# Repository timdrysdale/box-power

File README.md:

# box-power
circuit schematic for iso-container in-box DC-DC convertor support board.

### i6A4W

The DC-DC convertor is an adjustable, 250W, 9 to 53V Input Non-Isolated Step Down DC-DC Converter  [https://www.farnell.com/datasheets/3312958.pdf], which we purchased from Farnell.

The part does not exist in the standard KiCAD library. 

There is a "free" component design available [here](https://componentsearchengine.com/) but the license prevents redistribution, so I created the part from scratch.

## Pin Sizes

### Small

- pins DIA 1.02 [0.040] 
- standoffs DIA 1.78 [0.070]

### Large

- pins DIA 1.57 [0.062]
- standoffs DIA 2.59 [0.102]

## Hole sizes

[Samtec](https://www.samtec.com/support/pcb-hole-sizes) recommended hole sizes are as follows:

Lead size 1.14 [0.045] Dia hole 1.30 [0.051] Dia i.e 1.14x, or +0.16mm
Lead size 1.32 [0.052] Dia hole 1.47 [0.058] Dia i.e 1.12x, or +0.15mm

Most of the other entries show 0.15mm increase from pin to hole size, so not a percentage

[Practical Electronics](https://en.wikibooks.org/wiki/Practical_Electronics/PCB_Layout) recommends adding 6mils to round leads, i.e. 0.15mm.

[JLBPCB hole sizes](https://jlcpcb.com/capabilities/Capabilities) are 0.2mm -6.3mm
The tolerance is +0.13mm/-0.08mm

Minimum annular ring 2oz copper is 0.2mm, 0.3mm for PTH

It seems that the hole is enlarged in production ... so there is no need to allow for the PTH thickness?

so ...
pin size                    1.02   1.57
add 0.08mm tolerance        1.10   1.65
add 0.15mm clearance        1.17   1.72
next largest round 0.1mm    1.2    1.8

Also see IPC-7251, IPC-2222 and IPC-2221 for pad sizes as described [here](https://www.pcb-3d.com/tutorials/how-to-calculate-pth-hole-and-pad-diameter-sizes-according-to-ipc-7251-ipc-2222-and-ipc-2221-standards/)

The general density is level A, easiest to fabricate.
Pad Diameter = Minimum Hole Size + 0.1mm + 0.60mm (for Level A of IPC-2221)
So... 
1.2mm +0.1mm +0.6mm = 1.9mm diameter for the smaller pins
1.8 + 0.1mm +0.6mm = 2.5mm for the larger pins.

Y-offset of the pins 32, 33 is calculated as

reference up  to top of board 3.8mm
top of board to bottom of board 22.9mm
bottom of board up to holes 2.5mm
-- calculations
pin8 centreline down to bottom of board = 22.9-3.8mm = 19.1mm
pin8 centreline down to pin32 = 19.1mm - 2.5mm = 16.6mm

## Unconnected inputs

No optional features ordered (	I6A-4W0-20A-033V/001-R,)

### ON/OFF 

We ordered the 01 variant so negative logic on/off

Connect ON/OFF pin to ground  (see p19, remote on/off)

Consider derisking with a solder bridge option here?

### Power good

Leave open (see p20, top of  right column)

### Synchronization

Not a specified option, so leave open 32 SYNC, 33 MS

### Sequencing

Not an option - leave open.

### RUP

See p20 in datasheet, for 20A device.

5V 8k4 (should be 8k6, but this was the closest we could get, and will produce slightly higher voltage as typical of USB bus)

12V 1k82 

# Safety

## Fuse 30A

See p22 - select 30A fuse max, can choose smaller if you want.

# Footprints

Ordered from CPC Farnell 

### RC55Y-8K45BI 

RC55Y-8K45BI Through Hole Resistor, 8.45 kohm, RC Series, 250 mW, ± 0.1%, Axial Leaded, 350 V
	
8k45 trim resistor

L 7.2mm
D 2.5mm
lead 0.6 nom
PCB mounting centres 10.2mmm
Footprint: `Resistor_THT:R_Axial_DIN0207_L6.3mm_D2.5mm_P10.16mm_Horizontal`

### YR1B1K82CC 

YR1B1K82CC Through Hole Resistor, 1.82 kohm, R Series, 250 mW, ± 0.1%, Axial Leaded, 500 V

length 6.3mm +/- 0.3 
diameter 2.3 +/- 0.2
lead diamter 0.6mm nom

Can use same footprint as the other trim resistor

### 100uF

50YXF100MEFC8X11.5

8mm by 11.5mm

50V

8mm diameter
3.5 mm lead spacing
0.6mm lead diameter

Capacitor_THT:CP_Radial_D8.0mm_P3.50mm

### 21uF

50ML22MEFC8X5

8x5 variant (not 6.3x7)

diameter 8mm
Leg spacing 2.5mm 
leg diameter 0.45mm

Capacitor_THT:CP_Radial_D8.0mm_P2.50mm

### 0.1uF

MCMHR50V104M4X7 Electrolytic Capacitor, 0.1 µF, 50 V, MCMHR Series, ± 20%, Radial Leaded, 1000 hours @ 105°C

4mm OD by 7mm length
Leg spacing 1.5mm +/- 0.5mm
leads 0.45mm OD

Capacitor_THT:CP_Radial_D4.0mm_P1.50mm

### Fuse holder

Solder pins 0.5mm x 1.2mm

two holes 1.5mm diameter, spaced by 22.6mm

nearest existing footprint:
Fuse:Fuseholder_Cylinder-5x20mm_Schurter_0031_8201_Horizontal_Open
modified by enlarging holes to 1.5mm diameter (ends), 3.2mm middle:
box_power:Fuseholder_Cylinder-5x20mm_646_series_22.6_1.5

Ø 3mm screw hole may be used optionally - this is the central hole

### DC Plug

DC10B, DC Power Connector, Jack, 5 A, 2.5 mm

3.5mm by 1mm tines
5mm spacing between 1,3 and 2
13.55-7.4 = 6.15mm spacing between 1 and 3
1 is centre
3 is ground
2 is plug detect

CENTRE POSITIVE SO CAN BE UNPLUGGED LIVE

### USB A receptable

Multicomp

CONNFLY_DS1095_WNR0 is correct compared to the datasheet - renamed and put in box power for certainty later.

### Fan

12V Fan

40mm by 10.5mm
with 3.4mm diameter holes on 32mm centres
so use 2.5mm cable ties in 3.5 by 2mm holes
spaced 2mm from the fan

the leads are 26AWG, or 0.4038mm.

So the hole should be ... +0.23mm or 0.66mm diameter total, i.e 0.7mm drill
the pad should be 0.7mm bigger, or 1.4mm pad

# Track sizing

5mm track ok for 10A current and 20degC rise.

If we have 20A flowing, then temp rise will be closer to 85 degrees - however, this should not happen for long ....

### Parts from order

Part no.	Description	Quantity	Price
1	PW04096	24V 25A 600W Constant Voltage LED Driver, IP67 Rated - LED-DR-24V-600W-A	6	£172.32
2	2664687	I6A-4W0-20A-033V/001-R, Non Isolated POL DC/DC Converter, ITE, 250 W, 3.3 V, 15 V, 20 A, Adjustable	30	£22.47
3	2518207	CP30222SM In-Line Adapter, RJ45, RJ45, Adaptor, In-Line, FT Series, Jack, 8 Ways	30	£6.18
4	892373	NAC3MPA-1 High Power Connector, PowerCON Series, Receptacle, 250 VAC, 20 A, Panel Mount, Quick Connect	30	£2.80
5	892350	NAC3FCA High Power Connector, 3Pin, Blue, powerCON Series, Receptacle, 250 VAC, 20 A, Cable Mount, Screw	30	£4.94
6	2425457	Multicore Cable, Flexible Mains, 20, Per Metre, Unscreened, 2 Core, 2.5 mm² (one continuous length of 50m)	50	£1.96
7	224960	DC10B, DC Power Connector, Jack, 5 A, 2.5 mm, Through Hole Mount, Solder, pack of 10	10	£4.28
8	224935	DCPP2, DC Power Connector, Plug, 5 A, 9.5 mm, Cable Mount, Solder, pack of 10	10	£5.80
9	1871011	MCMHR50V104M4X7 Electrolytic Capacitor, 0.1 µF, 50 V, MCMHR Series, ± 20%, Radial Leaded, 1000 hours @ 105°C	50	£0.04
10	8126968	50ML22MEFC8X5 Electrolytic Capacitor, Miniature, 22 µF, 50 V, ML Series, ± 20%, Radial Leaded, 3000 hours @ 105°C	50	£0.15
11	1144634	50YXF100MEFC8X11.5 Electrolytic Capacitor, Miniature, 100 µF, 50 V, YXF Series, ± 20%, Radial Leaded	50	£0.17
12	2816685	MC002106 DC Axial Fan, 12 V, Square, 40 mm, 10.5 mm, Sleeve Bearing, 5.2 CFM	30	£1.76
13	1083279	YR1B1K82CC Through Hole Resistor, 1.82 kohm, R Series, 250 mW, ± 0.1%, Axial Leaded, 500 V	50	£0.37
14	9503005	RC55Y-8K45BI Through Hole Resistor, 8.45 kohm, RC Series, 250 mW, ± 0.1%, Axial Leaded, 350 V	10	£1.24
Total: £2911.34

# Track sizing thoughts....

if not using both sides of the board, better to go to 7mm AND 2oz copper, and keep temp rise down to 15deg.

# Reverse polarity protection

There are several options we can consider - just using a MOSFET, adding a ORING controller such LM5050 (not in stock at JLCPCB, no DIP package?), or IDP90PO3P4L-04 (check code!) as used in the infineon DC motor shield. The TI part LM5050 seems to use a number of external components.

Designing a simple MOSFET based system is described by [TI application note](https://www.ti.com/lit/an/slva139/slva139.pdf?ts=1637407408575).

Main consideration is getting low R_DS_ON, with power dissipation being R_DS_ON * I_LOAD.

world's lowest RDS_on at 30V, intended for reverse voltage protection:
https://www.infineon.com/dgdl/Infineon-I80P03P4L_04-DS-v01_01-en.pdf?fileId=db3a30431ddc9372011e07e95eb827d7

-80A continuous drain current
VGS+5/-16V ??
Ptot 137W
VDSmax for breakdown 30V
7mOhm x 10A = 7e-3x100 = 7x0.1 = 0.7W, compared to 240W total power, so <1% 

but not recommended for new designs

Maybe this:-
https://uk.farnell.com/vishay/sqp100p06-9m3l-ge3/mosfet-p-ch-60v-100a-175deg-c/dp/3470727

suggested safety margin of nearly x2 on VDS, and use of zener for protection of VDS
https://components101.com/articles/design-guide-pmos-mosfet-for-reverse-voltage-polarity-protection

lead size 1.01mm max, wide side of legs (wide side of body), 0.36 - 0.61mm narrow side 
spacing iunside to outside leg 2.4-2.67mm, outside legs 4.88 - 5.28mm (so 5mm nominal)

Pin order left to right from front: GDS 

package: TO 220AB

Connections:

VBAT goes to DRAIN
GATE Goes to resistor/zener junction
SOURCE goes to top of zener, and top of load.
bottom of resistor goes to ground.

See [Infineon Application note for tradeoffs between diode, N-channel with charge pump and P-channel](https://www.infineon.com/dgdl/Reverse-Batery-Protection-Rev2.pdf?fileId=db3a304412b407950112b41887722615)

Package_TO_SOT_THT:TO-220-3_Vertical

## Zener diode

Since VGS max is +/-20V, choose 18V Zener. 5% is 0.9V.

https://uk.farnell.com/nexperia/bzx79-c18-133/diode-zener-0-5w-18v-do-35/dp/1097219?st=zener%20diode

Body length 4.25mm, diameter 1.85mm, lead size 0.56mm max
DO-35

Diode_THT:D_DO-35_SOD27_P7.62mm_Horizontal

## bias resistor

Zener power dissipation is 500mW, so at 18V would be 27mA current max. Call it 20mA

Expect a reverse voltage of 24V, so 6V to drop across resistor. MAx current 20mA
V=IR so R = V/I = 6/20mA = 300R

this should be consistent with a fast enough switch for reverse polarity protection.

MFR4-300RFI 0.5W 6.2mm body length max, diamter 2.5mm professional version

Resistor_THT:R_Axial_DIN0207_L6.3mm_D2.5mm_P10.16mm_Horizontal

## HEATSINK

possibly this one....

	MC33278

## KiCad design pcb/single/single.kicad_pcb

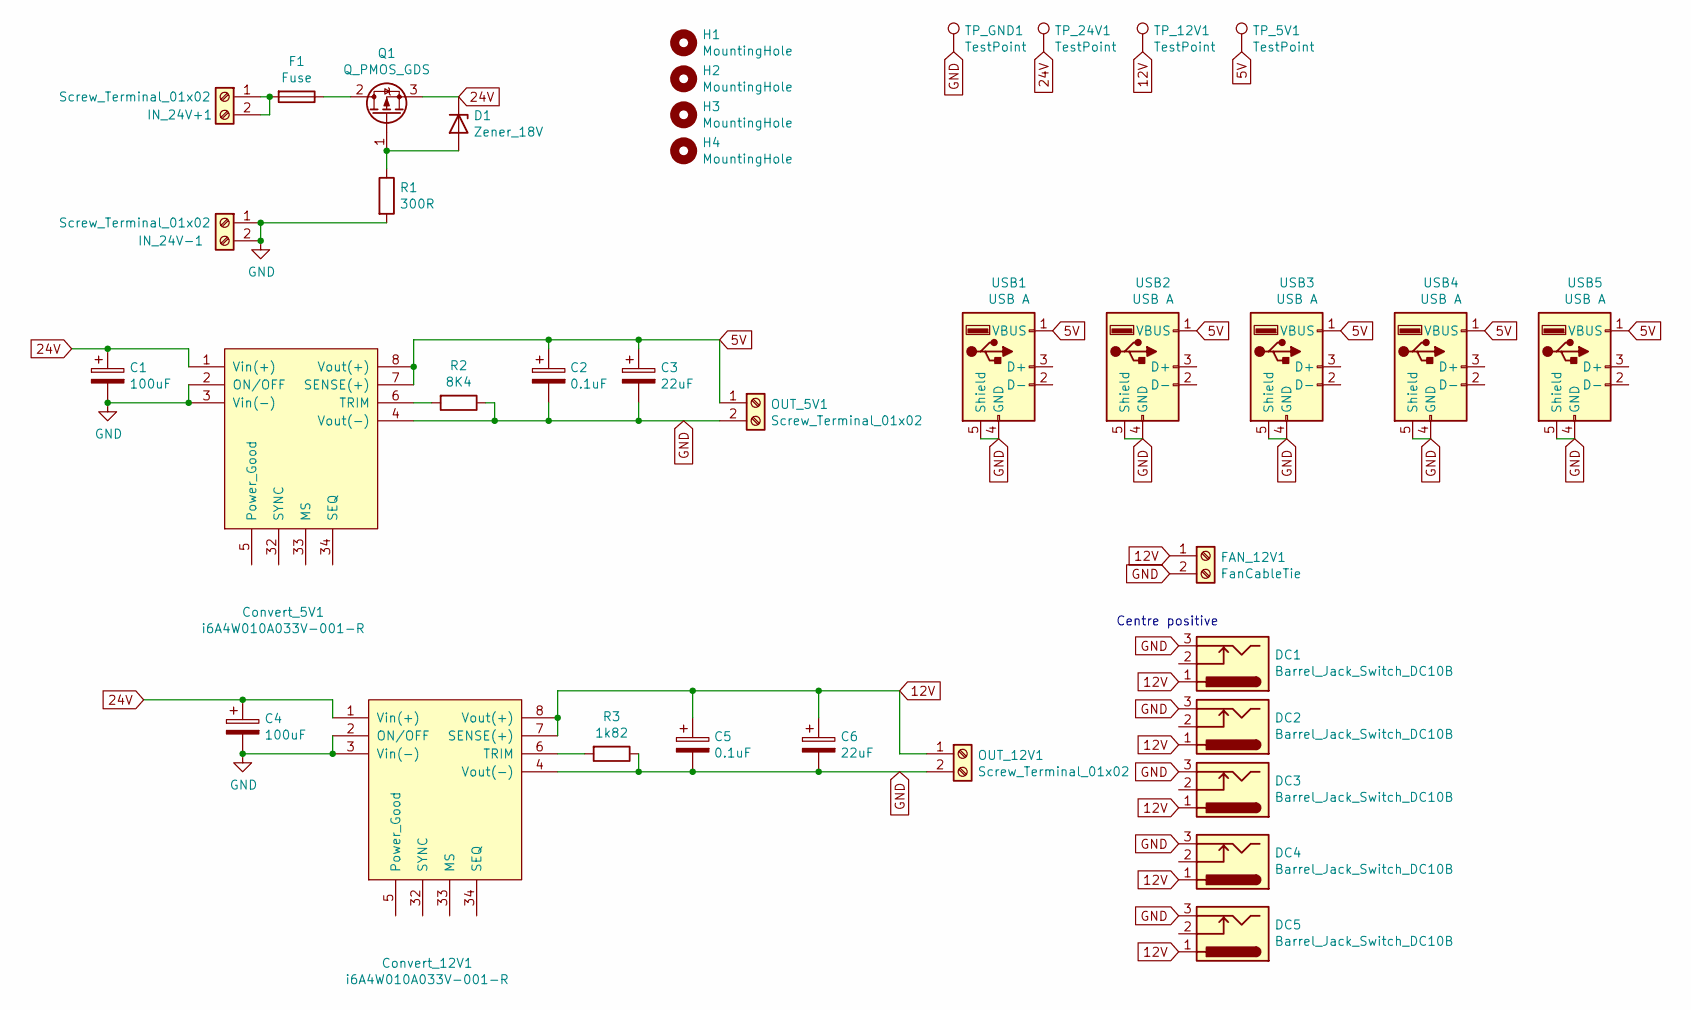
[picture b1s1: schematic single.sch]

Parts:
C1, C4: 100uF; CP_Radial_D8.0mm_P3.50mm
C2, C5: 0.1uF; CP_Radial_D4.0mm_P1.50mm
C3, C6: 22uF; CP_Radial_D8.0mm_P2.50mm
Convert_5V1, Convert_12V1: i6A4W010A033V-001-R; i6A4W-DIP
D1: Zener_18V; D_DO-35_SOD27_P7.62mm_Horizontal
DC1, DC2, DC3, DC4, DC5: Barrel_Jack_Switch_DC10B; BarrelJack_Horizontal_DC10B
F1: Fuse; Fuseholder_Cylinder-5x20mm_646_series_22.6_1.5
FAN_12V1: FanCableTie; Fan12V_40by10.5mm
H1, H2, H3, H4: MountingHole; MountingHole_3.2mm_M3
IN_24V+1, IN_24V-1: Screw_Terminal_01x02; TerminalBlock_bornier-2_P5.08mm
OUT_5V1, OUT_12V1: Screw_Terminal_01x02; TerminalBlock_bornier-2_P5.08mm
Q1: Q_PMOS_GDS; TO-220-3_Vertical
R1: 300R; R_Axial_DIN0207_L6.3mm_D2.5mm_P10.16mm_Horizontal
R2: 8K4; R_Axial_DIN0207_L6.3mm_D2.5mm_P10.16mm_Horizontal
R3: 1k82; R_Axial_DIN0207_L6.3mm_D2.5mm_P10.16mm_Horizontal
TP_5V1, TP_12V1, TP_24V1: TestPoint; TestPoint_Pad_D4.0mm
TP_GND1: TestPoint; TestPoint_Pad_D4.0mm
USB1, USB2, USB3, USB4, USB5: USB A; USB_A_CONNFLY_DS1095-WNR0

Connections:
5V: C2.1, C3.1, Convert_5V1.7 (SENSE(+)), Convert_5V1.8 (Vout(+)), OUT_5V1.1, TP_5V1.1, USB1.1 (VBUS), USB2.1 (VBUS), USB3.1 (VBUS), USB4.1 (VBUS), USB5.1 (VBUS)
12V: C5.1, C6.1, Convert_12V1.7 (SENSE(+)), Convert_12V1.8 (Vout(+)), DC1.1, DC2.1, DC3.1, DC4.1, DC5.1, FAN_12V1.1, OUT_12V1.1, TP_12V1.1
24V: C1.1, C4.1, Convert_5V1.1 (Vin(+)), Convert_12V1.1 (Vin(+)), D1.1 (K), Q1.3 (S), TP_24V1.1
GND: C1.2, C2.2, C3.2, C4.2, C5.2, C6.2, Convert_5V1.2 (ON/OFF), Convert_5V1.3 (Vin(-)), Convert_5V1.4 (Vout(-)), Convert_12V1.2 (ON/OFF), Convert_12V1.3 (Vin(-)), Convert_12V1.4 (Vout(-)), DC1.3, DC2.3, DC3.3, DC4.3, DC5.3, FAN_12V1.2, IN_24V-1.1, IN_24V-1.2, OUT_5V1.2, OUT_12V1.2, R1.2, R2.1, R3.1, TP_GND1.1, USB1.4 (GND), USB1.5 (Shield), USB2.4 (GND), USB2.5 (Shield), USB3.4 (GND), USB3.5 (Shield), USB4.4 (GND), USB4.5 (Shield), USB5.4 (GND), USB5.5 (Shield)
unnamed: Convert_5V1.6 (TRIM), R2.2
unnamed: Convert_12V1.6 (TRIM), R3.2
unnamed: D1.2 (A), Q1.1 (G), R1.1
unnamed: F1.1, Q1.2 (D)
unnamed: F1.2, IN_24V+1.1, IN_24V+1.2

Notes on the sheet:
Centre positive

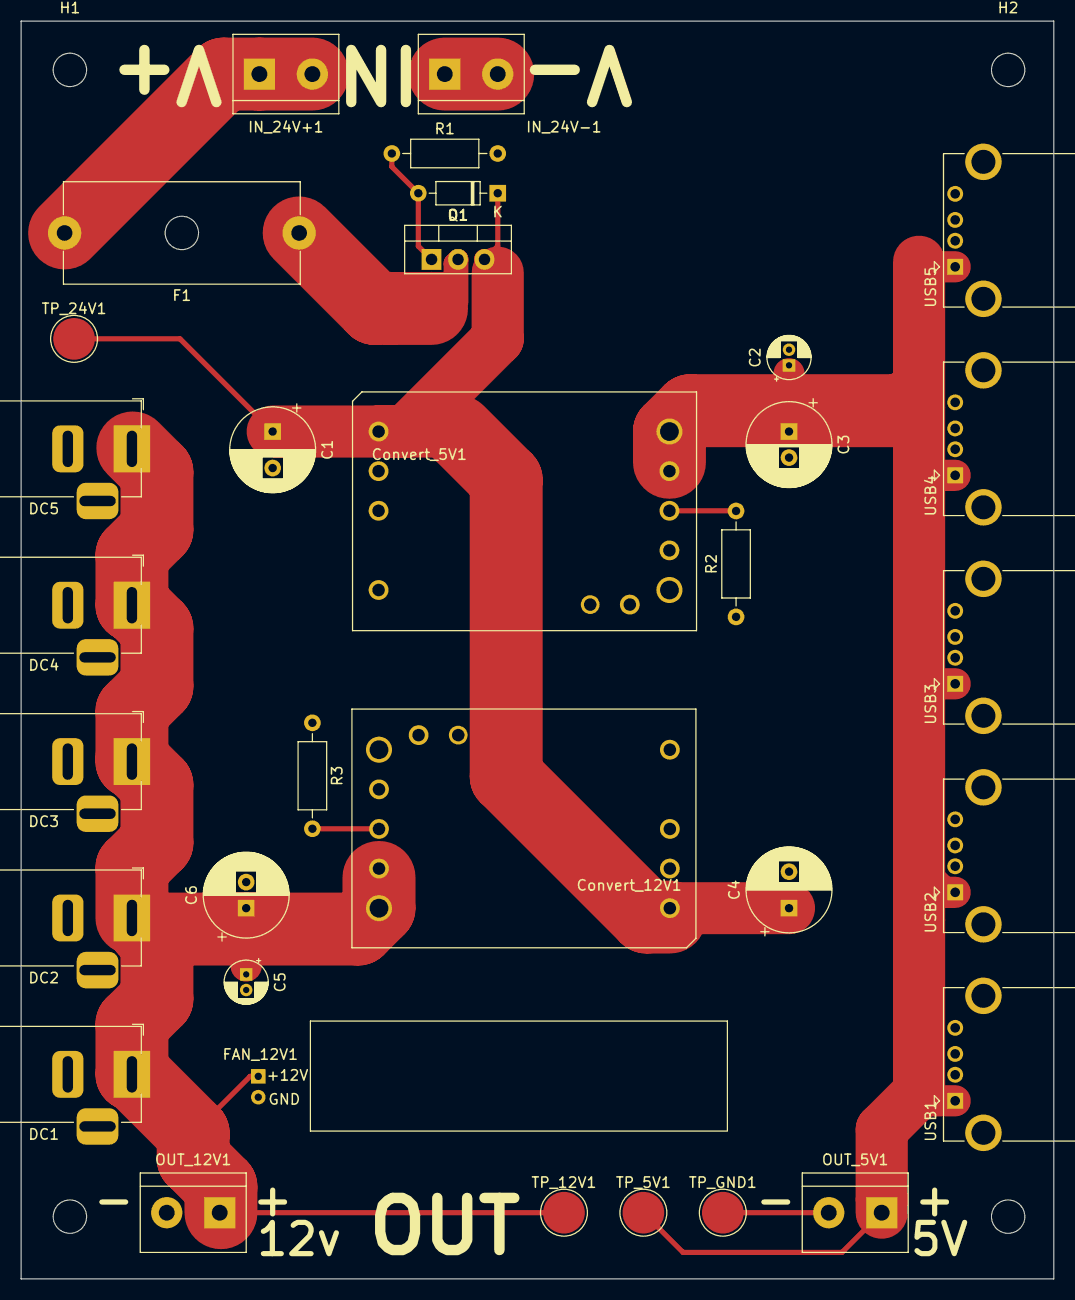
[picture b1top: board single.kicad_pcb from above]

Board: 2 copper layers, 99.1 x 120.7 mm, 37 parts (0 on the bottom side), 9 nets.

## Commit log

2021-11-08 Add schematic symbol for i6A4
2021-11-20 First routing attempt
2021-12-06 As ordered
2021-12-17 remove js
